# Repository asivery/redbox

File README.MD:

# RedBOX

The open-source programmer for Renesas GreenPAK chips with OTP memory.

## Project layout

- `hardware` - contains the schematics and sample PCB design for the programmer
- `software/host` - contains the program which you should run on your PC to communicate with the RedBOX board
- `software/usb` - contains the program which should be written to the RP2040 board

## Compatibility list

**TODO**

Right now no library files are published, as I still need to do more testing before I publish any of them.

## Technical

### Connection with the programmer

The RedBOX programming software communicates with the RedBOX board using a vendor USB interface - make sure you have the appropriate device drivers installed (and access rules set up). 

### The GreenPAK protocol

In the GreenPAK ICs, the OTP is programmed with the help of PCTL and PROG pins. In order to force the GreenPAK into a programming mode, one needs to apply 7.5V to the PROG pin. Even if programmed to disable the built-in I2C interface, after applying that voltage, the GreenPAK should report back, if queried over I2C.

I have observed that before writing the actual program, the Renesas dev board sends a particular sequence, which I decided to call the init sequence, to the chip. I do not know if that is something that needs to be sent to the chip before programming or not, but since the memory is one-time-programmable I decided not to verify that and instead faithfully recreated that initialization sequence's timings in the RP2040 code. Should the need arise, it is possible to define more initialization sequences - the one I mentioned has the ID of `0`. Every GreenPAK description file should define what init sequence the chip uses.

#### Programming the GreenPAK

To program the GreenPAK, one needs to first send the initialization sequence, then bring up power and the 7.5V on `PROG`.
Afterwards, the `PCTL` pin should be set high, and finally the program can be sent over I2C, with the appropriate padding at the front and end of the memory image.

#### Reading data back

To read the program back, one can simply send the first address of the region to be read back, and start reading data over I2C. If the OTP-written program disabled I2C, the data can still be read after sending 7.5V to the `PROG` pin.
**The chip's I2C ID might change in comparison to what it had been before writing OTP!**

It is possible to disable the ability to read the program bytes from the GreenPAK. If this feature is enabled in the image written to the OTP, the program bytes will instead get read back as `0xFF`.

## Credits

- [Pico_WS2812](https://github.com/ForsakenNGS/Pico_WS2812) - Library for controlling the LED on the RP2040 board
- [RP2040-Zero-Kicad](https://github.com/CountParadox/RP2040-Zero-Kicad), [MT3608-module-kicad](https://github.com/barafael/MT3608-module-kicad) - KiCad symbols and footprints for the Waveshare RP2040 Zero board and MT3608 boost converter

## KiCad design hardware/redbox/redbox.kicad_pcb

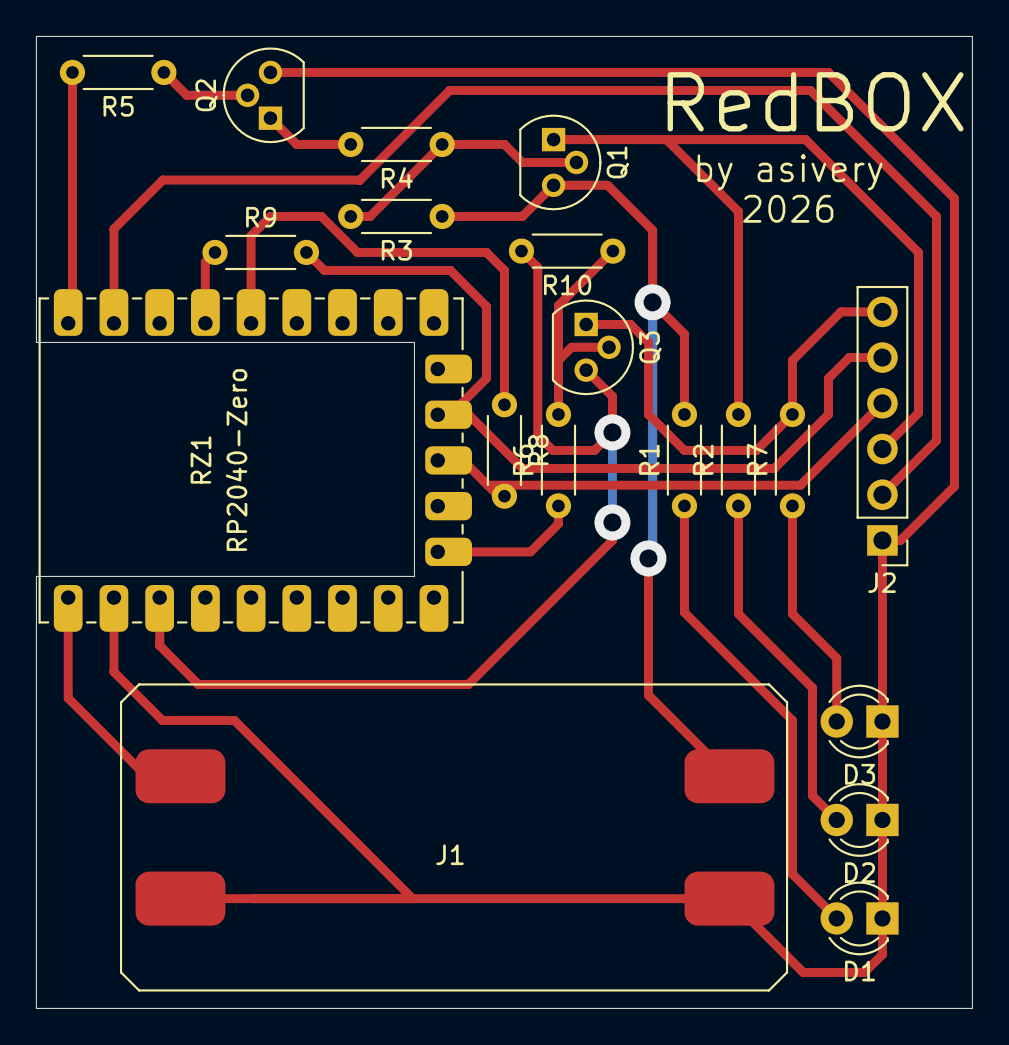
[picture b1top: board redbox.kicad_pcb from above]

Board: 2 copper layers, 52.0 x 54.0 mm, 19 parts (0 on the bottom side), 20 nets.

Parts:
D1, D2, D3: LED; LED_D3.0mm
J1: Boost; hw-045
J2: Conn_01x06_Pin; PinHeader_1x06_P2.54mm_Vertical
Q1, Q3: PNP; TO-92
Q2: NPN; TO-92
R1, R2, R3, R4, R5, R6, R7, R8, R9, R10: R; R_Axial_DIN0204_L3.6mm_D1.6mm_P5.08mm_Horizontal
RZ1: RP2040-Zero

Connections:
unnamed: D1.2 (A), R1.1
unnamed: D1.1 (K), D2.1 (K), D3.1 (K), J1.1, J1.4, J2.1, Q2.3 (E), RZ1.22 (GND)
unnamed: D2.2 (A), R2.1
unnamed: D3.2 (A), R7.1
unnamed: J1.2, RZ1.23 (5V)
unnamed: J1.3, Q1.3 (E), R1.2, R3.1
unnamed: J2.2, RZ1.2 (GP1)
unnamed: J2.3, Q1.1 (C), R2.2
unnamed: J2.4, R8.2, RZ1.12 (GP11)
unnamed: J2.5, R9.2, RZ1.11 (GP10)
unnamed: J2.6, Q3.1 (C), R7.2
unnamed: Q1.2 (B), R3.2, R4.1
unnamed: Q2.2 (B), R5.1
unnamed: Q2.1 (C), R4.2
unnamed: Q3.2 (B), R6.2, R10.1
unnamed: Q3.3 (E), R10.2, RZ1.21 (3V3)
unnamed: R5.2, RZ1.1 (GP0)
unnamed: R9.1, RZ1.4 (GP3)
unnamed: R8.1, RZ1.5 (GP4)
unnamed: R6.1, RZ1.14 (GP13)
